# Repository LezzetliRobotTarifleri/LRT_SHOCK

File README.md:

# LRT_SHOCK
Real users will feel real pain at games.

LRT_SHOCK projesi farklı oyunlardan oyuncunun can verisini çekerek bu veriye bağlı olarak gerçek hayatta elektrik şoku alarak acı çekmesini ve farklı bir deneyim elde etmesini amaçlayan açık kaynak kodlu deneysel bir projedir ve youtube/lezzetlirobottarifleri kanalında yayınlanmaktadır.

Proje hakkındaki güncellemeler https://www.youtube.com/lezzetlirobottarifleri kanalından takip edilebilir.

Proje her ne kadar eğlence amaçlı tasarlanmış olsada tehlikeli bir projedir ve 15 yaş altı, 50 yaş üstü, herhangi bir sağlık sorunu olan kişiler, hamileler, kalp pili kullananlar ve elektronik konusunda amatör olan kişiler tarafından kullanılmamalıdır. 

Kurulum aşamaları için bu video şimdilik iş görür:
https://www.youtube.com/watch?v=wtrCjeJp03g&feature=youtu.be

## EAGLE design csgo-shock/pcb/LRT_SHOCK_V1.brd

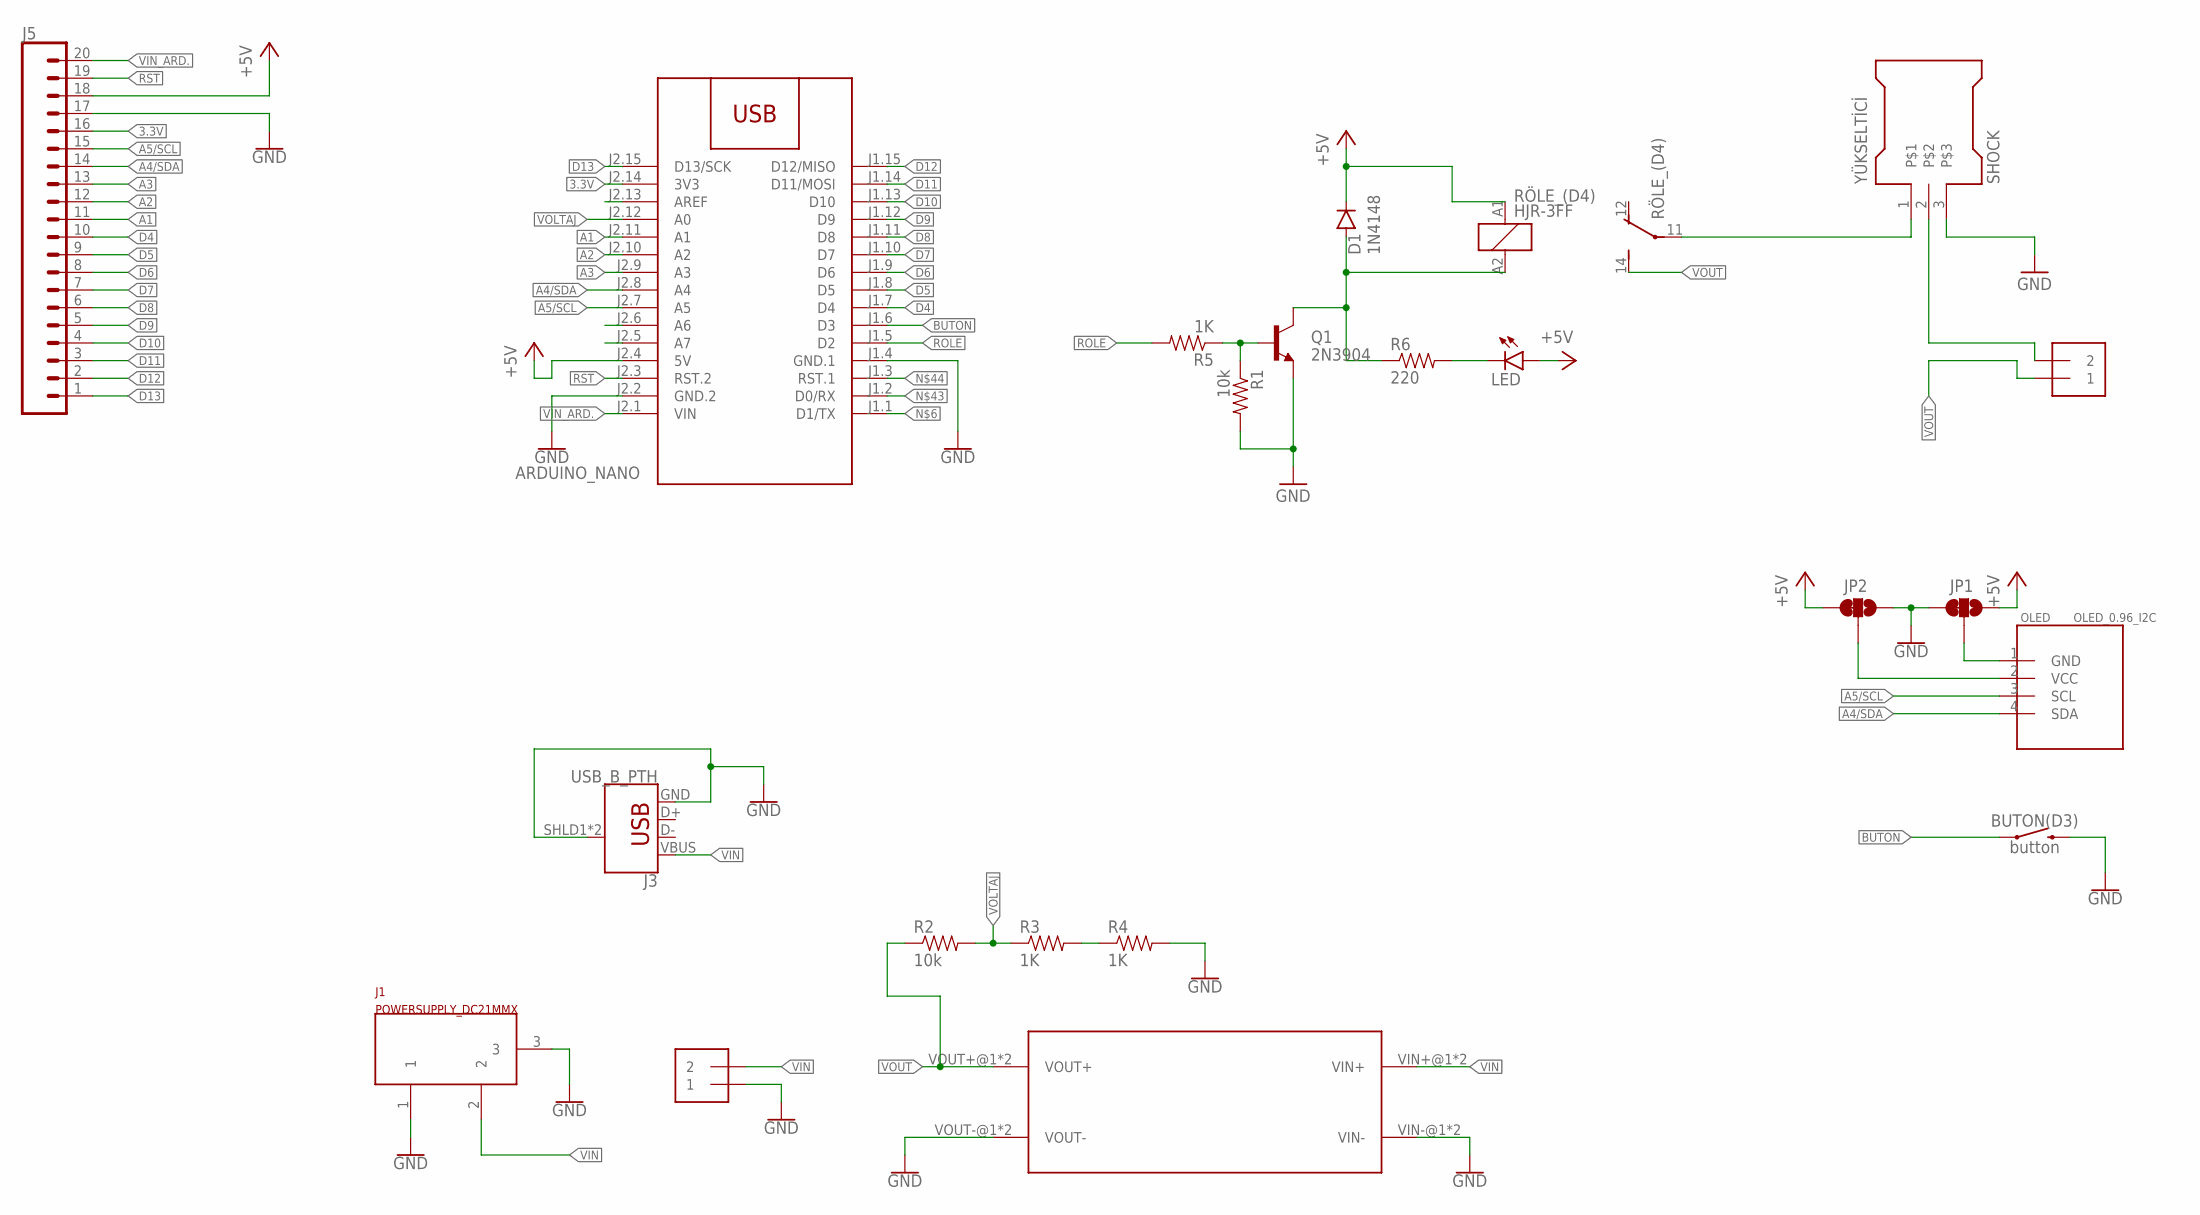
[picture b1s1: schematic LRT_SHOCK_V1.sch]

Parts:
ARDUINO_NANO: ARDUINO-NANO
BUTON(D3): button; TACTILE_SWITCH_PTH_12MM
D1: 1N4148; DIODE-1N4148-KIT
J1: POWERSUPPLY_DC21MMX; POWERSUPPLY_DC-21MM
J2: 1X2-3.5MM
J3: USB_B_PTH; USB-B-PTH
J5: CONN_20; 1X20
JP1, JP2: JUMPER-SMT_3_1-NC_TRACE_SILK; SMT-JUMPER_3_1-NC_TRACE_SILK
LED: LED5MM-KIT
MT3608: MT3608MT3608_2; MT3608_2
OLED: OLED_0.96_I2C
Q1: 2N3904; TO-92-EZ
R1, R2: 10k; AXIAL-0.3EZ
R3, R4, R5: 1K; AXIAL-0.3EZ
R6: 220; AXIAL-0.3EZ
RÖLE_(D4): HJR-3FF; ZN5
SHOCK!!: 1X2-3.5MM
YÜKSELTİCİ: SHOCK

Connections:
3.3V: ARDUINO_NANO.J2.14 (3V3), J5.16
+5V: ARDUINO_NANO.J2.4 (5V), D1.C, J5.18, JP1.1, JP2.3, LED.A, RÖLE_(D4).A1 (1)
A1: ARDUINO_NANO.J2.11 (A1), J5.11
A2: ARDUINO_NANO.J2.10 (A2), J5.12
A3: ARDUINO_NANO.J2.9 (A3), J5.13
A4/SDA: ARDUINO_NANO.J2.8 (A4), J5.14, OLED.4 (SDA)
A5/SCL: ARDUINO_NANO.J2.7 (A5), J5.15, OLED.3 (SCL)
BUTON: ARDUINO_NANO.J1.6 (D3), BUTON(D3).1
D4: ARDUINO_NANO.J1.7 (D4), J5.10
D5: ARDUINO_NANO.J1.8 (D5), J5.9
D6: ARDUINO_NANO.J1.9 (D6), J5.8
D7: ARDUINO_NANO.J1.10 (D7), J5.7
D8: ARDUINO_NANO.J1.11 (D8), J5.6
D9: ARDUINO_NANO.J1.12 (D9), J5.5
D10: ARDUINO_NANO.J1.13 (D10), J5.4
D11: ARDUINO_NANO.J1.14 (D11/MOSI), J5.3
D12: ARDUINO_NANO.J1.15 (D12/MISO), J5.2
D13: ARDUINO_NANO.J2.15 (D13/SCK), J5.1
GND: ARDUINO_NANO.J1.4 (GND.1), ARDUINO_NANO.J2.2 (GND.2), BUTON(D3).3 (2), J1.1, J1.3, J2.1, J3.GND, J3.SHLD1 (SHIELD), J3.SHLD2 (SHIELD), J5.17, JP1.3, JP2.1, MT3608.VIN-@1 (VIN-), MT3608.VIN-@2 (VIN-), Q1.1 (E), R1.P$2 (2), R4.P$2 (2), YÜKSELTİCİ.3
unnamed: MT3608.VOUT-@1 (VOUT-), MT3608.VOUT-@2 (VOUT-)
unnamed: SHOCK!!.2, YÜKSELTİCİ.2
unnamed: R3.P$2 (2), R4.P$1 (1)
unnamed: JP1.2, OLED.1 (GND)
unnamed: D1.A, Q1.3 (C), R6.P$1 (1), RÖLE_(D4).A2 (2)
unnamed: Q1.2 (B), R1.P$1 (1), R5.P$1 (1)
unnamed: LED.K (C), R6.P$2 (2)
unnamed: RÖLE_(D4).11, YÜKSELTİCİ.1
unnamed: JP2.2, OLED.2 (VCC)
ROLE: ARDUINO_NANO.J1.5 (D2), R5.P$2 (2)
RST: ARDUINO_NANO.J2.3 (RST.2), J5.19
VIN: J1.2, J2.2, J3.VBUS, MT3608.VIN+@1 (VIN+), MT3608.VIN+@2 (VIN+)
VIN_ARD.: ARDUINO_NANO.J2.1 (VIN), J5.20
VOLTAJ: ARDUINO_NANO.J2.12 (A0), R2.P$2 (2), R3.P$1 (1)
VOUT: MT3608.VOUT+@1 (VOUT+), MT3608.VOUT+@2 (VOUT+), R2.P$1 (1), RÖLE_(D4).14 (S), SHOCK!!.1

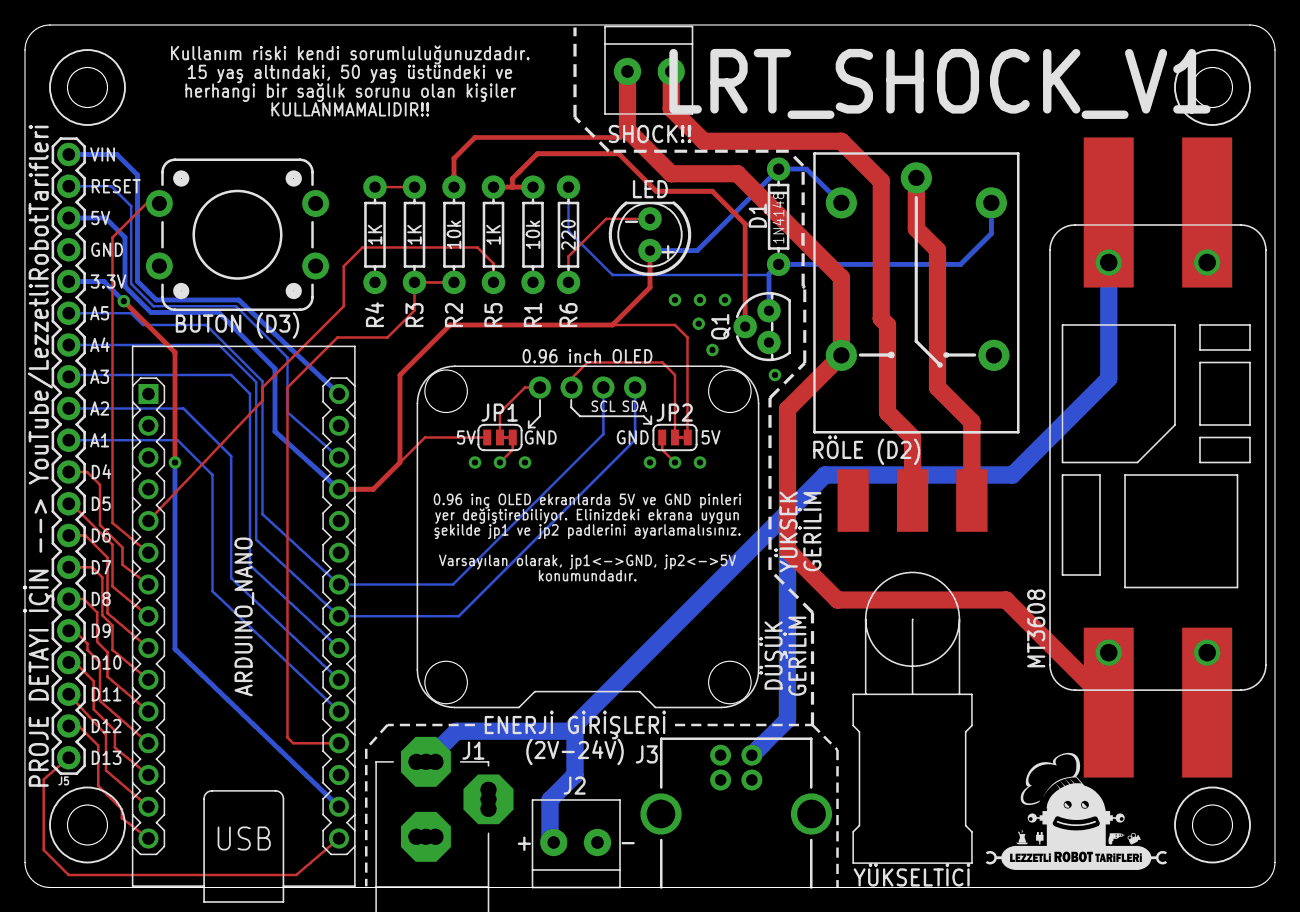
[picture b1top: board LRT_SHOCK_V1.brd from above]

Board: 2 copper layers, 100.0 x 69.0 mm, 24 parts (1 on the bottom side), 34 nets.

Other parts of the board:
U$3: LRT-LOGO-0,0125-B
U$4: LRT-LOGO-0,10416-B-N_I

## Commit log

2020-12-31 update main.go location
2020-12-31 refactor
2021-02-07 add CLI parameters
2021-02-09 added * to health
2021-02-19 redesign folders
2021-02-19 rm DS Store
2021-02-19 added .keep
2021-02-19 Delete .keep
    cleaning

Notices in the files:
parts and their libraries:
SparkFun-Switches: Licensing: Creative Commons ShareAlike 4.0 International - https://creativecommons.org/licenses/by-sa/4.0
SparkFun-Aesthetics: Licensing: CC v3.0 Share-Alike You are welcome to use this library for commercial purposes.
